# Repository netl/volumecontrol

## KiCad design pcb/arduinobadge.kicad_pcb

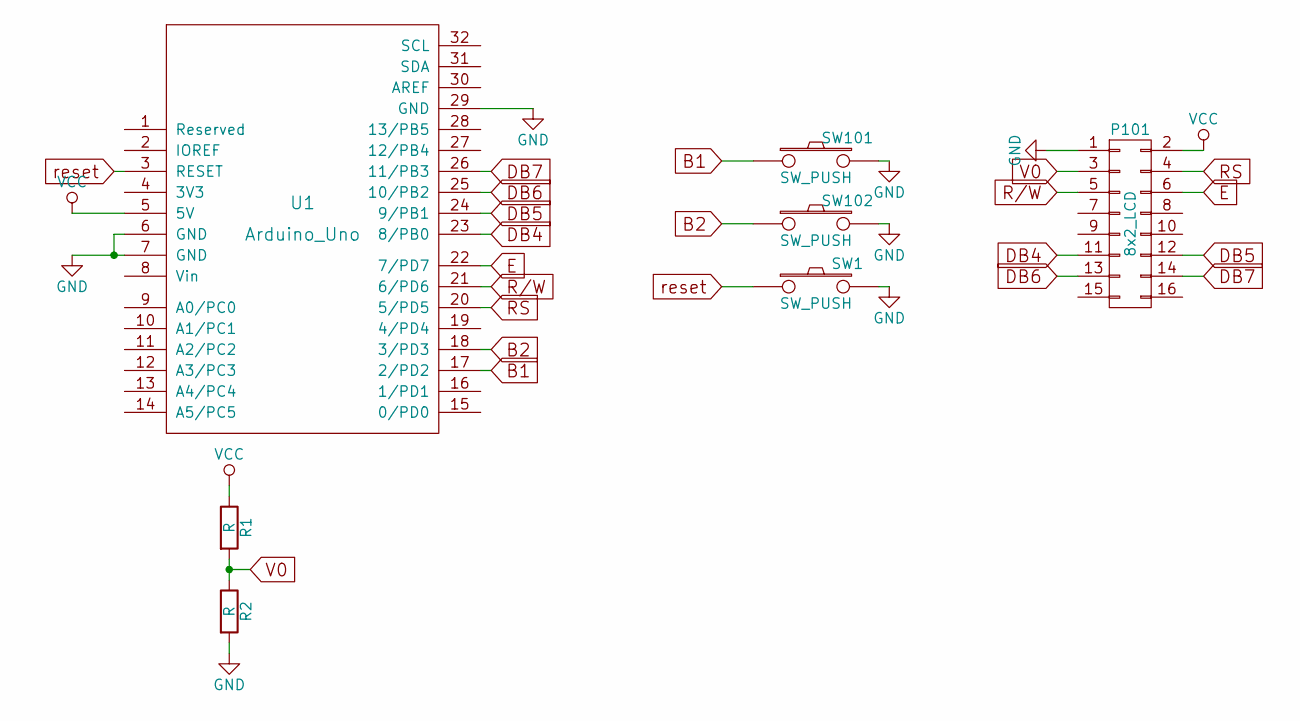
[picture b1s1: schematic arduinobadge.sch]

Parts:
P101: 8x2_LCD
R1, R2: R; SMD_0603
SW1, SW101, SW102: SW_PUSH; SW_DIP_x1_Slide
U1: Arduino_Uno; Arduino_uno

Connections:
B1: SW101.1, U1.17 (2/PD2)
B2: SW102.1, U1.18 (3/PD3)
DB4: P101.11, U1.23 (8/PB0)
DB5: P101.12, U1.24 (9/PB1)
DB6: P101.13, U1.25 (10/PB2)
DB7: P101.14, U1.26 (11/PB3)
E: P101.6, U1.22 (7/PD7)
GND: P101.1, R2.2, SW1.2, SW101.2, SW102.2, U1.6 (GND), U1.7 (GND), U1.29 (GND)
R/W: P101.5, U1.21 (6/PD6)
RS: P101.4, U1.20 (5/PD5)
V0: P101.3, R1.2, R2.1
VCC: P101.2, R1.1, U1.5 (5V)
reset: SW1.1, U1.3 (RESET)

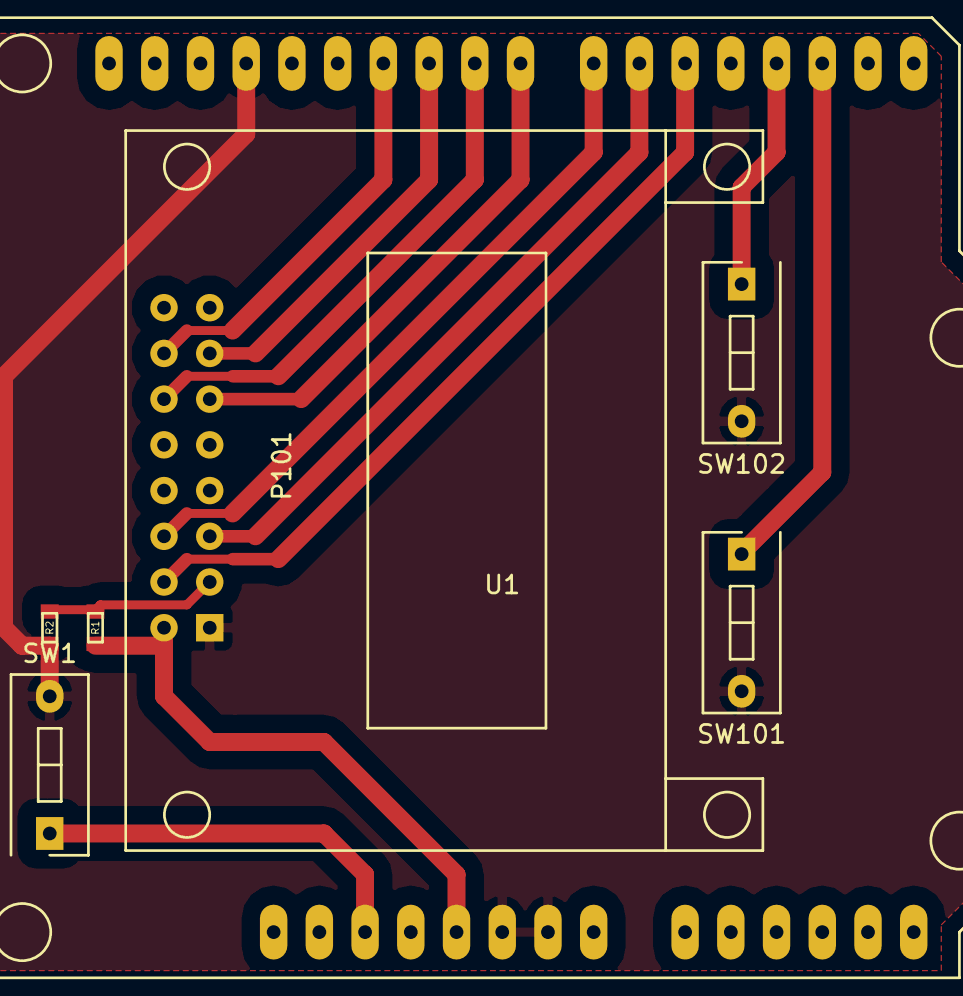
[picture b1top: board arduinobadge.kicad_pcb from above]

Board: 2 copper layers, 7 parts (0 on the bottom side), 13 nets.
